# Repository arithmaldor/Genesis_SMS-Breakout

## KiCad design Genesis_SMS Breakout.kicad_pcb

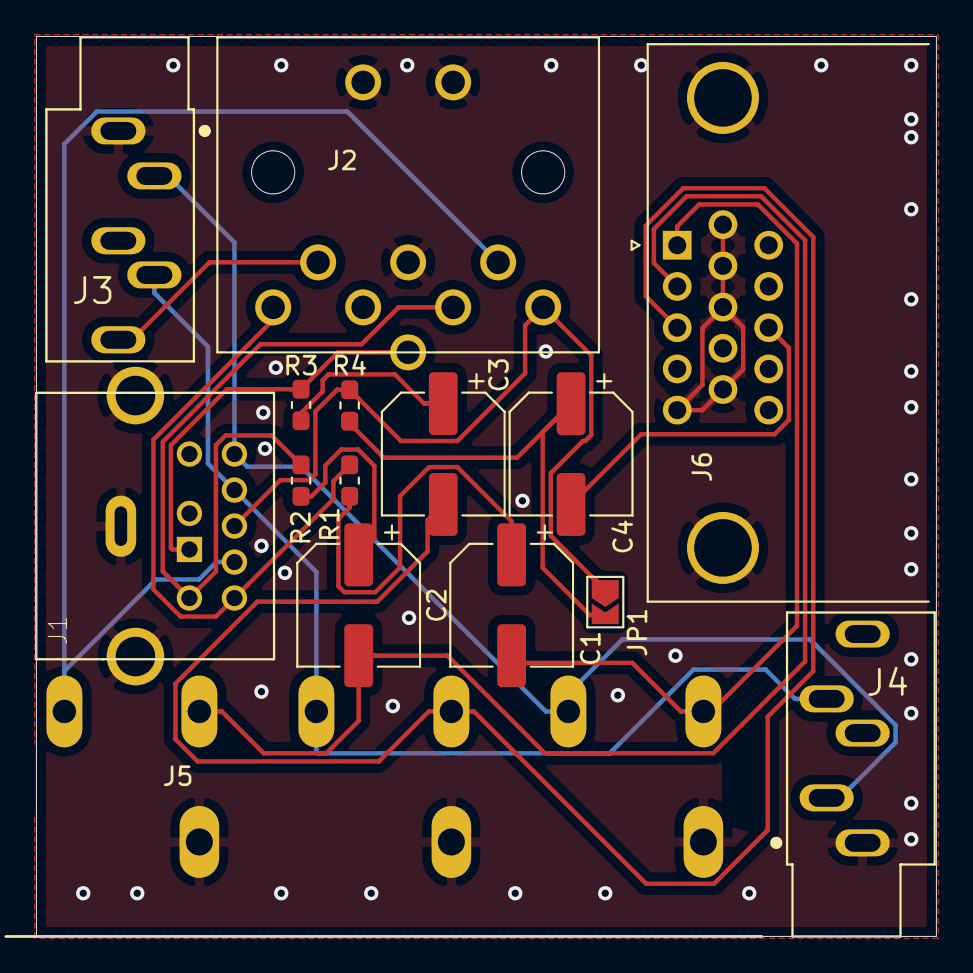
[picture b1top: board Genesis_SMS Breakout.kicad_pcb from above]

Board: 2 copper layers, 50.0 x 50.0 mm, 15 parts (0 on the bottom side), 17 nets.

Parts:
C1, C2, C3, C4: 220; CP_Elec_6.3x5.4
J1: Conn_01x09_Female; CUI_MD-90SM
J2: Conn_01x08_Female; 262_U_DIN_MAB_8_SH
J3, J4: AudioJack3_SwitchTR; CUI_SJ1-3533NG
J5: Conn_01x09_Female; 3x2_RCA
J6: DB15_Female_HighDensity_MountingHoles; VGA
JP1: Jumper_NO_Small; SolderJumper-2_P1.3mm_Open_TrianglePad1.0x1.5mm
R1, R2, R3: 75; R_0603_1608Metric_Pad1.05x0.95mm_HandSolder
R4: 470; R_0603_1608Metric_Pad1.05x0.95mm_HandSolder

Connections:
BLUE: J1.1, J2.6, R3.2
BLUE_OUT: C3.2, J5.4, J6.3
CSYNC: J1.5, J2.8, JP1.1, R4.2
CVBS: J1.4, J2.3, J5.1
GND: J1.S, J1.S1, J2.0, J2.2, J3.S, J4.S, J5.7, J5.8, J5.9, J6.0, J6.5, J6.6, J6.7, J6.8, J6.10
GREEN: J1.3, J2.5, R2.2
GREEN_OUT: C2.2, J5.2, J6.2
LEFT: J1.8, J3.T, J4.T, J5.3
MONO: J2.1, J3.TS
unnamed: C1.1, R1.1
unnamed: C2.1, R2.1
unnamed: C3.1, R3.1
unnamed: C4.1, JP1.2, R4.1
RED: J1.7, J2.7, R1.2
RED_OUT: C1.2, J5.6, J6.1
RIGHT: J1.9, J3.R, J4.R, J5.5
VGA_SYNC_OUT: C4.2, J6.13

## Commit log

2019-07-13 Finished layout
    finished PCB design, generated gerbers and renders
2019-07-29 zipped gerbers
